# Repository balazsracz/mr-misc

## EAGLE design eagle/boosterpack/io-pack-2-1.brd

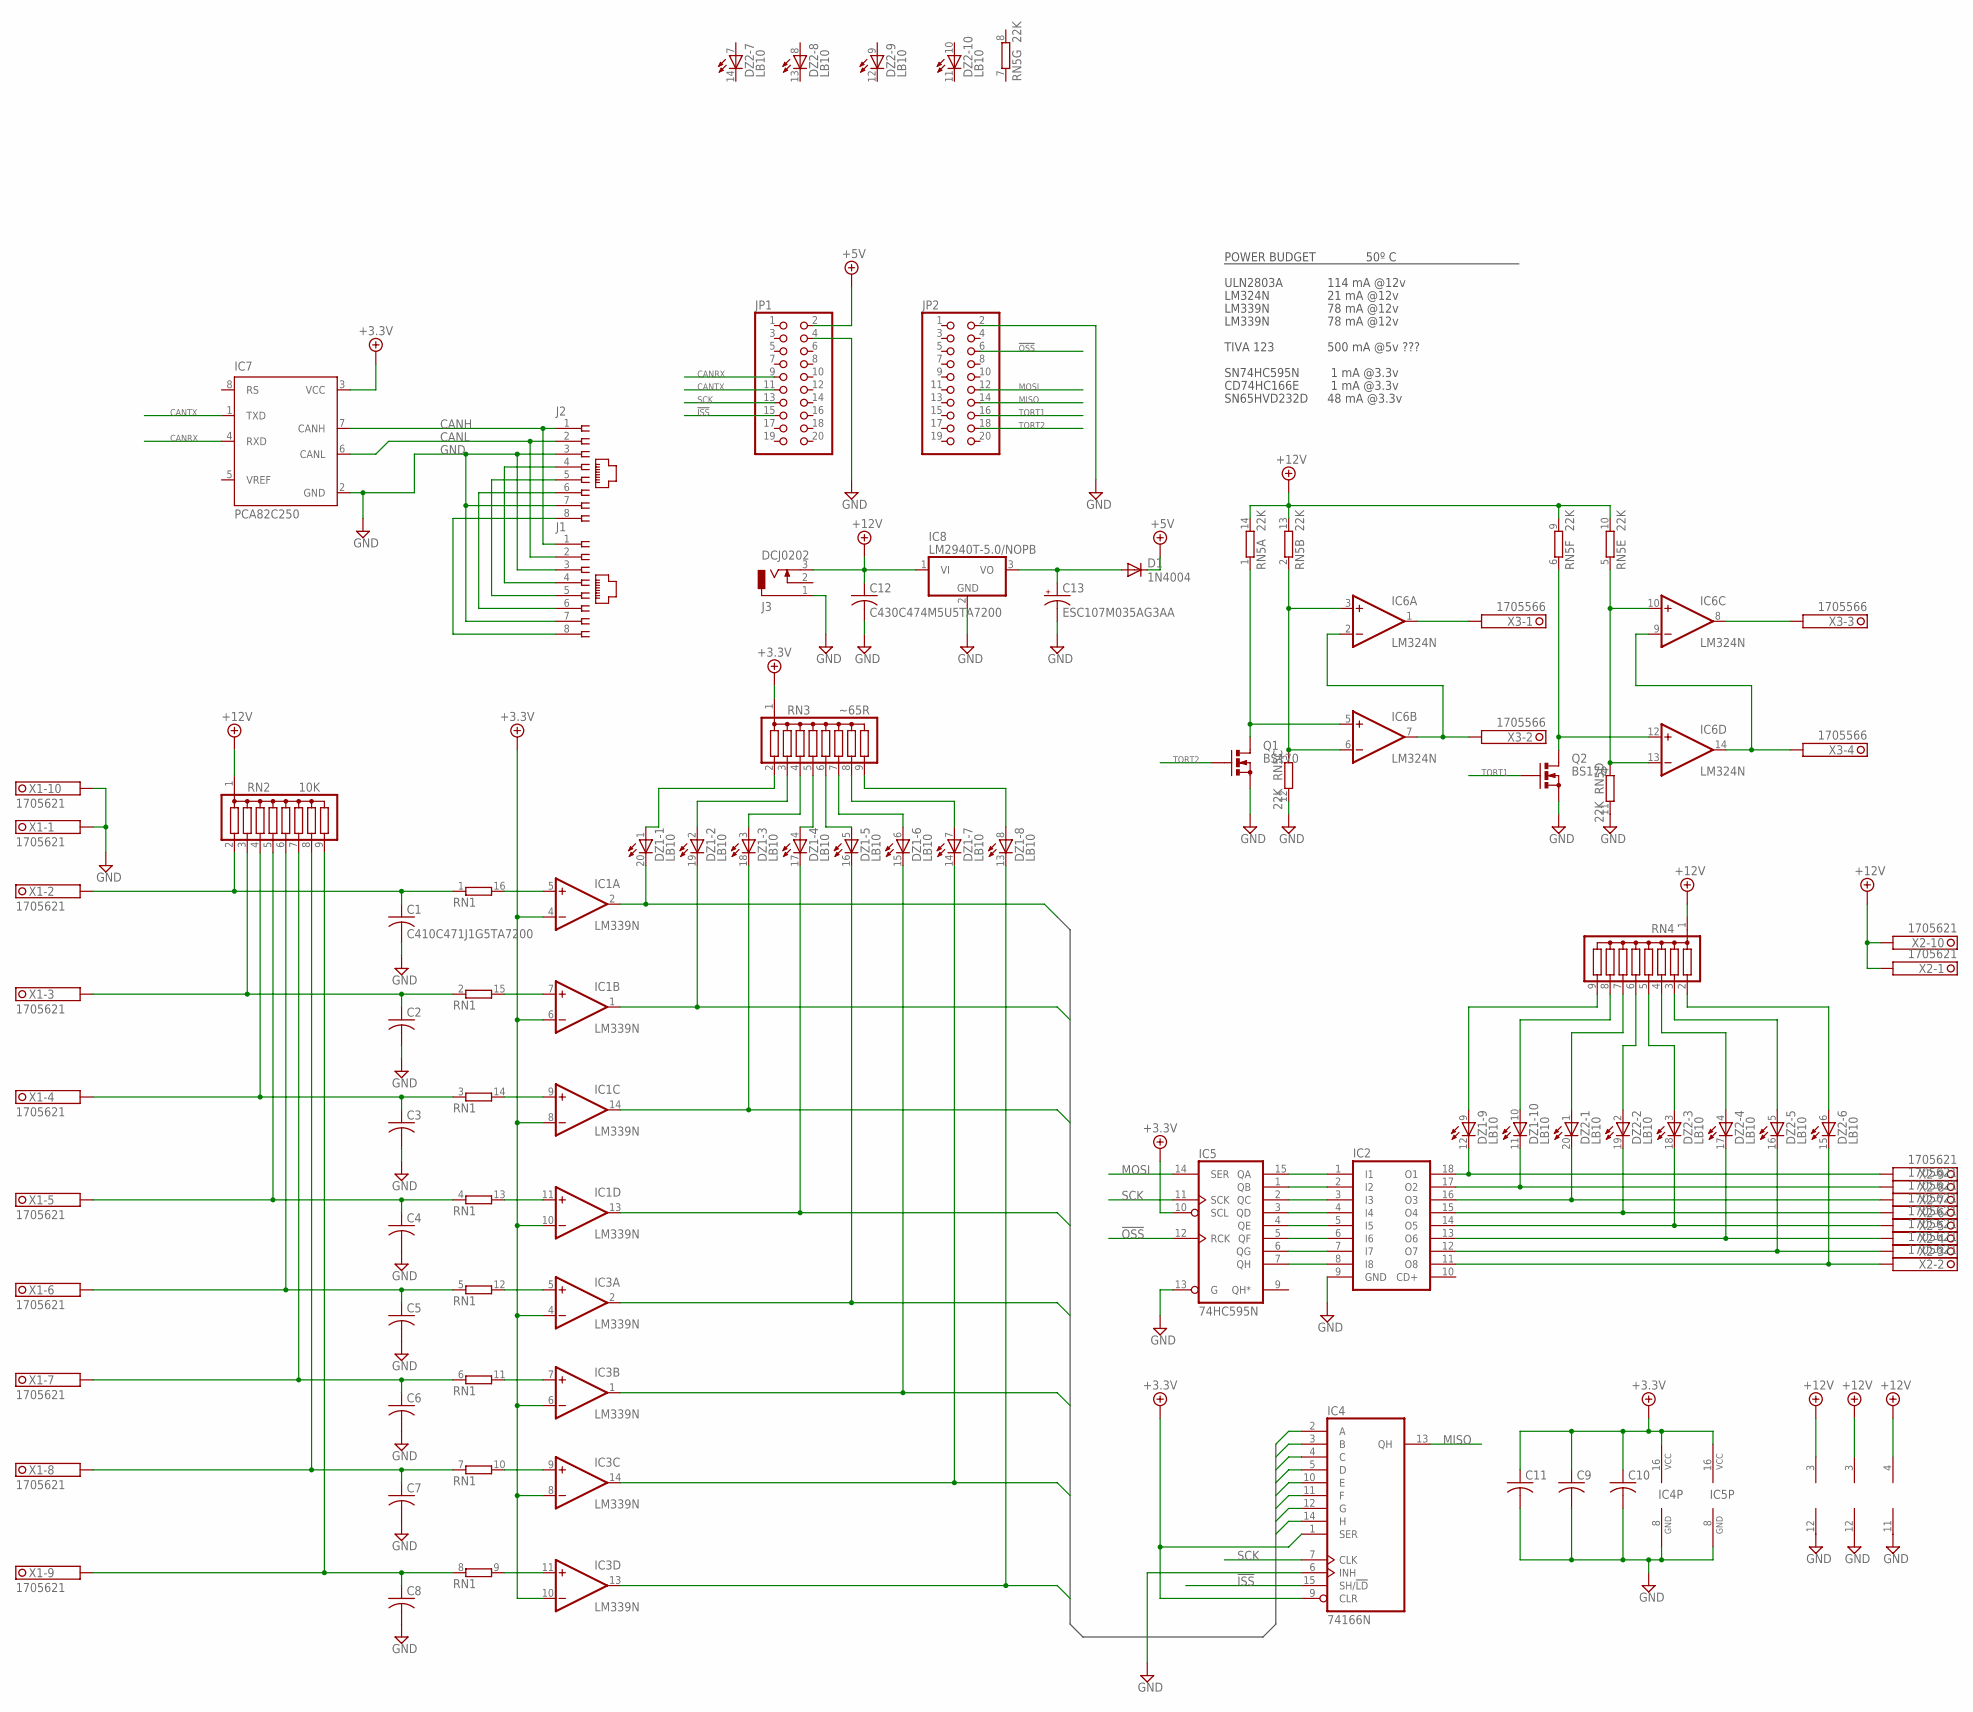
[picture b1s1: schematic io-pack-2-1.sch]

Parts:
C1: C410C471J1G5TA7200; C050-025X075
C2, C3, C4, C5, C6, C7, C8, C9, C10, C11: C-US050-025X075; C050-025X075
C12: C430C474M5U5TA7200; C075-032X103
C13: ESC107M035AG3AA; E3,5-8
D1: 1N4004; DO41-10
DZ1, DZ2: LB10
IC1, IC3: LM339N; DIL14
IC2: ULN2803A; DIL18
IC4: 74166N; DIL16
IC5: 74HC595N; DIL16
IC6: LM324N; DIL14
IC7: PCA82C250; DIL08
IC8: LM2940T-5.0/NOPB; TO220V
J1, J2: 555164-1
J3: DCJ0202
JP1, JP2: PINHD-2X10; 2X10
Q1, Q2: BS170; SOT54E
RN1: 8R-P; DIL16
RN2: 10K; SIL9
RN3: ~65R; SIL9
RN4: G08R; SIL9
RN5: 22K; DIL14
X1, X2: 1705621
X3: 1705566

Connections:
!ISS: IC4.15 (SH/!LD), JP1.15
!OSS: IC5.12 (RCK), JP2.6
+3.3V: C9.1, C10.1, C11.1, IC1.4 (-IN), IC1.6 (-IN), IC1.8 (-IN), IC1.10 (-IN), IC3.4 (-IN), IC3.6 (-IN), IC3.8 (-IN), IC3.10 (-IN), IC4.1 (SER), IC4.9 (CLR), IC4.16 (VCC), IC5.10 (SCL), IC5.16 (VCC), IC7.3 (VCC), RN3.1
+5V: D1.C, JP1.2
+12V: C12.1, IC1.3 (V+), IC3.3 (V+), IC6.4 (V+), IC8.1 (VI), J3.3, RN2.1, RN4.1, RN5.9 (2), RN5.10 (2), RN5.13 (2), RN5.14 (2), X2.1.1, X2.1.2, X2.10.1, X2.10.2
CANH: IC7.7 (CANH), J1.1, J2.1
CANL: IC7.6 (CANL), J1.2, J2.2
CANRX: IC7.4 (RXD), JP1.9
CANTX: IC7.1 (TXD), JP1.11
GND: C1.2, C2.2, C3.2, C4.2, C5.2, C6.2, C7.2, C8.2, C9.2, C10.2, C11.2, C12.2, C13.-, IC1.12 (GND), IC2.9 (GND), IC3.12 (GND), IC4.6 (INH), IC4.8 (GND), IC5.8 (GND), IC5.13 (G), IC6.11 (V-), IC7.2 (GND), IC8.2 (GND), J1.3, J1.7, J2.3, J2.7, J3.1, JP1.4, JP2.2, Q1.S, Q2.S, RN5.11 (2), RN5.12 (2), X1.1.1, X1.1.2, X1.10.1, X1.10.2
IN0: DZ1.20 (C), IC1.2 (OUT), IC4.2 (A)
IN1: DZ1.19 (C), IC1.1 (OUT), IC4.3 (B)
IN2: DZ1.18 (C), IC1.14 (OUT), IC4.4 (C)
IN3: DZ1.17 (C), IC1.13 (OUT), IC4.5 (D)
IN4: DZ1.16 (C), IC3.2 (OUT), IC4.10 (E)
IN5: DZ1.15 (C), IC3.1 (OUT), IC4.11 (F)
IN6: DZ1.14 (C), IC3.14 (OUT), IC4.12 (G)
IN7: DZ1.13 (C), IC3.13 (OUT), IC4.14 (H)
MISO: IC4.13 (QH), JP2.14
MOSI: IC5.14 (SER), JP2.12
unnamed: C13.+, D1.A, IC8.3 (VO)
unnamed: J1.4, J2.4
unnamed: J1.5, J2.5
unnamed: J1.6, J2.6
unnamed: IC1.5 (+IN), RN1.16 (2)
unnamed: IC1.7 (+IN), RN1.15 (2)
unnamed: IC1.9 (+IN), RN1.14 (2)
unnamed: IC1.11 (+IN), RN1.13 (2)
unnamed: DZ1.1 (A), RN3.2
unnamed: DZ1.2 (A), RN3.3
unnamed: DZ1.3 (A), RN3.4
unnamed: DZ1.4 (A), RN3.5
unnamed: DZ1.5 (A), RN3.6
unnamed: DZ1.6 (A), RN3.7
unnamed: DZ1.7 (A), RN3.8
unnamed: DZ1.8 (A), RN3.9
unnamed: IC2.1 (I1), IC5.15 (QA)
unnamed: IC2.2 (I2), IC5.1 (QB)
unnamed: IC2.3 (I3), IC5.2 (QC)
unnamed: IC2.4 (I4), IC5.3 (QD)
unnamed: C1.1, RN1.1, RN2.2, X1.2.1, X1.2.2
unnamed: C2.1, RN1.2 (1), RN2.3, X1.3.1, X1.3.2
unnamed: C3.1, RN1.3 (1), RN2.4, X1.4.1, X1.4.2
unnamed: C4.1, RN1.4 (1), RN2.5, X1.5.1, X1.5.2
unnamed: IC3.5 (+IN), RN1.12 (2)
unnamed: IC3.7 (+IN), RN1.11 (2)
unnamed: IC3.9 (+IN), RN1.10 (2)
unnamed: IC3.11 (+IN), RN1.9 (2)
unnamed: C5.1, RN1.5 (1), RN2.6, X1.6.1, X1.6.2
unnamed: C6.1, RN1.6 (1), RN2.7, X1.7.1, X1.7.2
unnamed: C7.1, RN1.7 (1), RN2.8, X1.8.1, X1.8.2
unnamed: C8.1, RN1.8 (1), RN2.9, X1.9.1, X1.9.2
unnamed: IC2.5 (I5), IC5.4 (QE)
unnamed: IC2.6 (I6), IC5.5 (QF)
unnamed: IC2.7 (I7), IC5.6 (QG)
unnamed: IC2.8 (I8), IC5.7 (QH)
unnamed: IC6.3 (+IN), IC6.6 (-IN), RN5.2 (1), RN5.3 (1)
unnamed: DZ1.12 (C), IC2.18 (O1), X2.9.1, X2.9.2
unnamed: DZ1.9 (A), RN4.9
unnamed: DZ1.10 (A), RN4.8
unnamed: DZ2.1 (A), RN4.7
unnamed: DZ2.2 (A), RN4.6
unnamed: DZ2.3 (A), RN4.5
unnamed: DZ2.4 (A), RN4.4
unnamed: DZ2.5 (A), RN4.3
unnamed: DZ2.6 (A), RN4.2
unnamed: DZ1.11 (C), IC2.17 (O2), X2.8.1, X2.8.2
unnamed: DZ2.20 (C), IC2.16 (O3), X2.7.1, X2.7.2
unnamed: DZ2.19 (C), IC2.15 (O4), X2.6.1, X2.6.2
unnamed: DZ2.18 (C), IC2.14 (O5), X2.5.1, X2.5.2
unnamed: DZ2.17 (C), IC2.13 (O6), X2.4.1, X2.4.2
unnamed: DZ2.16 (C), IC2.12 (O7), X2.3.1, X2.3.2
unnamed: DZ2.15 (C), IC2.11 (O8), X2.2.1, X2.2.2
unnamed: IC6.5 (+IN), Q1.D, RN5.1
unnamed: IC6.2 (-IN), IC6.7 (OUT), X3.2.1, X3.2.2
unnamed: IC6.12 (+IN), Q2.D, RN5.6 (1)
unnamed: IC6.10 (+IN), IC6.13 (-IN), RN5.4 (1), RN5.5 (1)
unnamed: IC6.9 (-IN), IC6.14 (OUT), X3.4.1, X3.4.2
unnamed: IC6.1 (OUT), X3.1.1, X3.1.2
unnamed: IC6.8 (OUT), X3.3.1, X3.3.2
PWR_POS: J1.8, J2.8
SCK: IC4.7 (CLK), IC5.11 (SCK), JP1.13
TORT1: JP2.16, Q2.G
TORT2: JP2.18, Q1.G

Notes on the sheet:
POWER BUDGET
ULN2803A
114 mA @12v
50º C
LM324N
21 mA @12v
LM339N
78 mA @12v
SN74HC595N
CD74HC166E
SN65HVD232D
TIVA 123
1 mA @3.3v
48 mA @3.3v
500 mA @5v ???

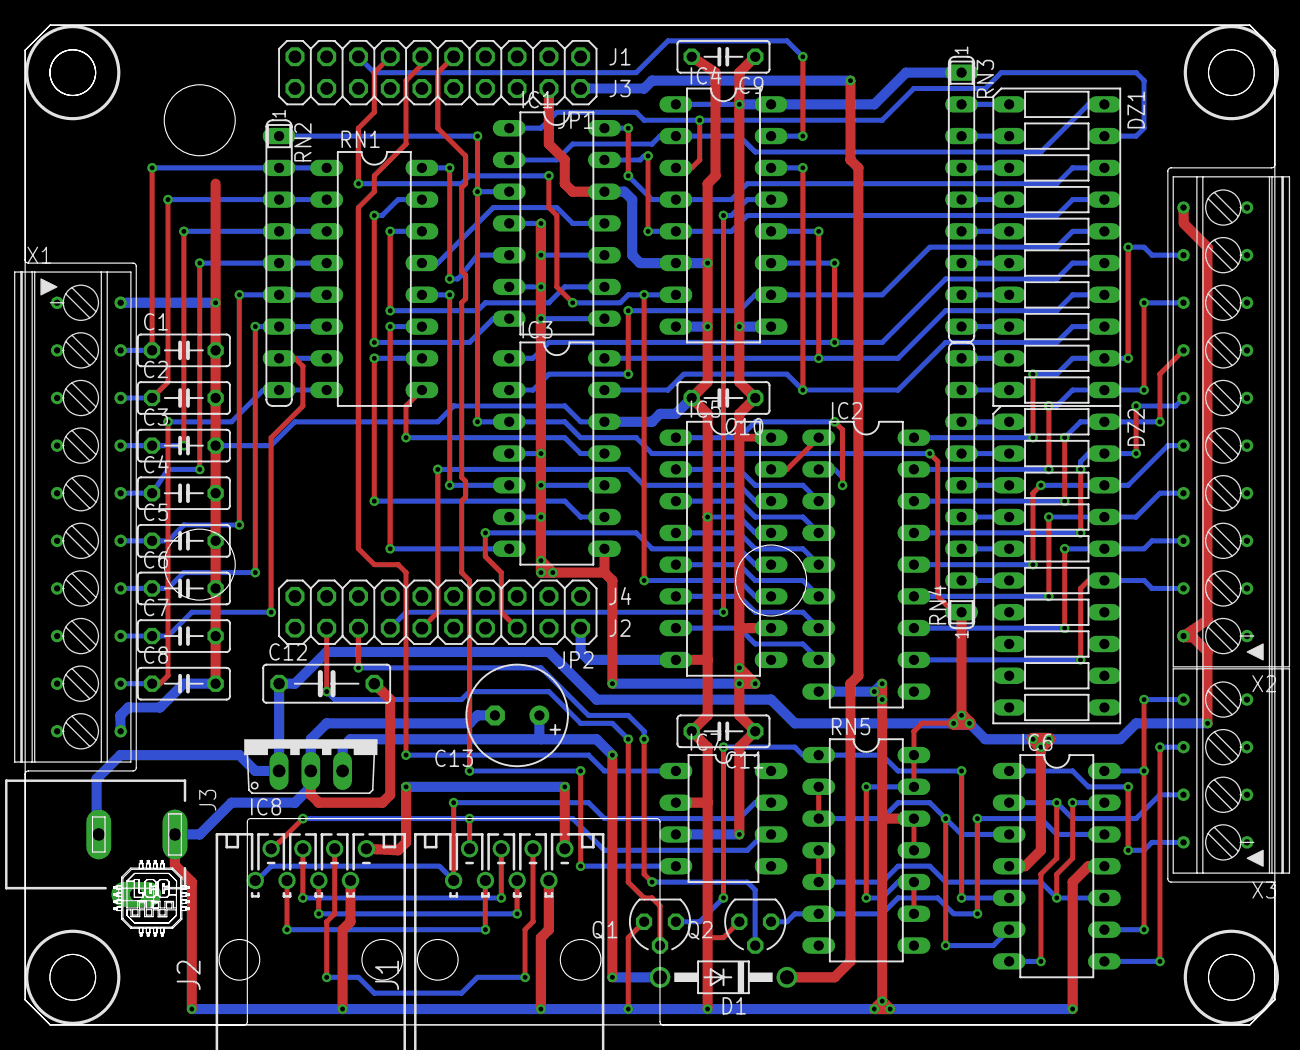
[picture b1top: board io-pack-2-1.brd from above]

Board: 2 copper layers, 100.0 x 80.0 mm, 39 parts (0 on the bottom side), 84 nets.

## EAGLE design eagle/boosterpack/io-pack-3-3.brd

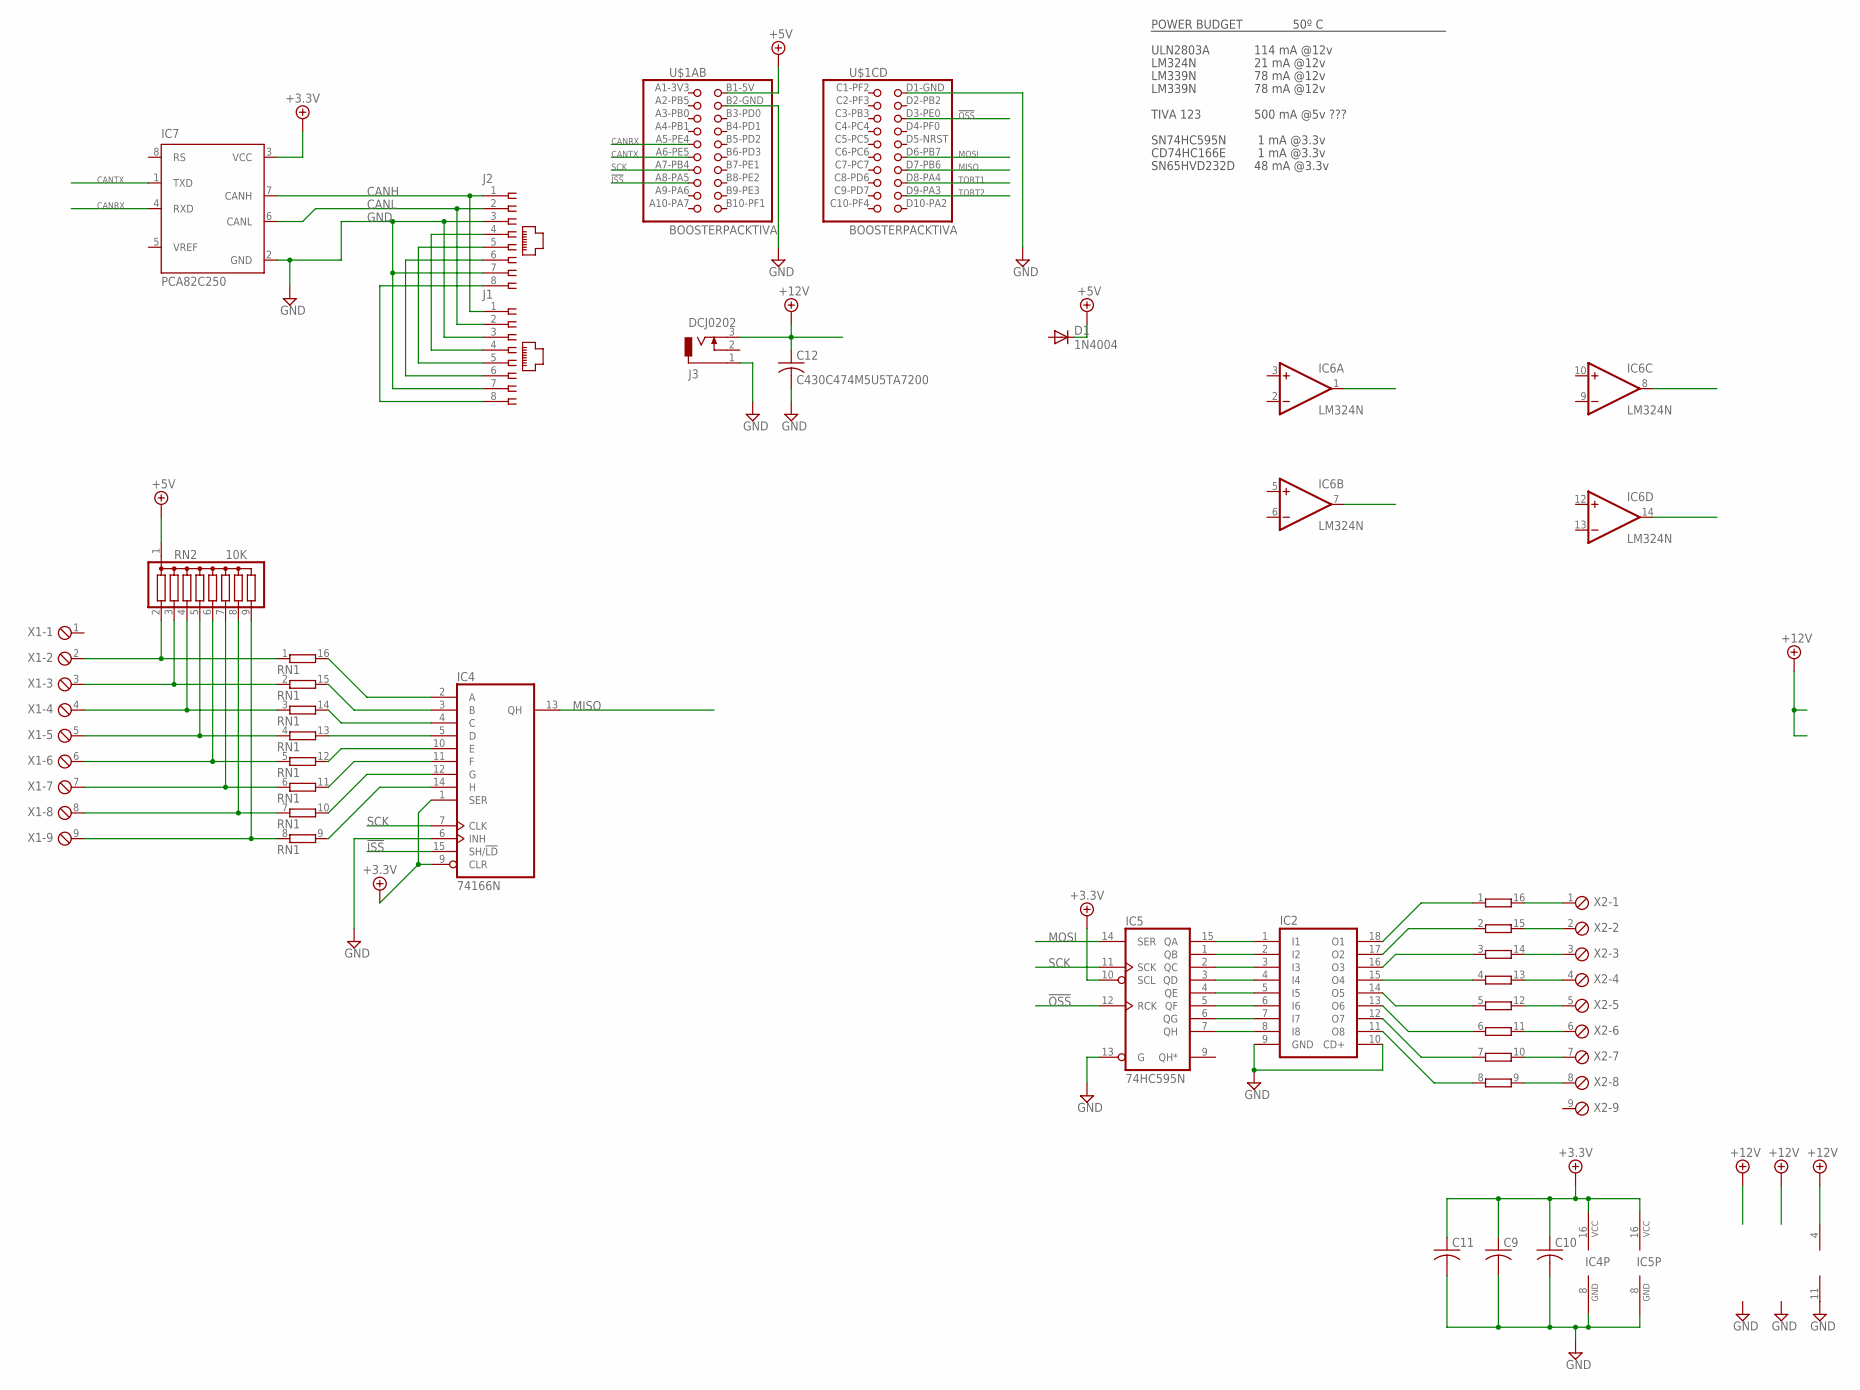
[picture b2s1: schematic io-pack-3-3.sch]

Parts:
C9, C10, C11: C-US050-025X075; C050-025X075
C12: C430C474M5U5TA7200; C075-032X103
D1: 1N4004; DO41-10
IC2: ULN2803A; DIL18
IC4: 74166N; DIL16
IC5: 74HC595N; DIL16
IC6: LM324N; DIL14
IC7: PCA82C250; DIL08
J1, J2: 555164-1
J3: DCJ0202
RN1, RN3: 8R-P; DIL16
RN2: 10K; SIL9
U$1: BOOSTERPACKTIVA; BOOSTERPACK-TIVA
X1, X2: MPT9; 9POL254

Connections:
!ISS: IC4.15 (SH/!LD), U$1.A8-PA5 (15)
!OSS: IC5.12 (RCK), U$1.D3-PE0 (6)
+3.3V: C9.1, C10.1, C11.1, IC4.1 (SER), IC4.9 (CLR), IC4.16 (VCC), IC5.10 (SCL), IC5.16 (VCC), IC7.3 (VCC)
+5V: D1.C, RN2.1, U$1.B1-5V (2)
+12V: C12.1, IC6.4 (V+), J3.3
CANH: IC7.7 (CANH), J1.1, J2.1
CANL: IC7.6 (CANL), J1.2, J2.2
CANRX: IC7.4 (RXD), U$1.A5-PE4 (9)
CANTX: IC7.1 (TXD), U$1.A6-PE5 (11)
GND: C9.2, C10.2, C11.2, C12.2, IC2.9 (GND), IC2.10 (CD+), IC4.6 (INH), IC4.8 (GND), IC5.8 (GND), IC5.13 (G), IC6.11 (V-), IC7.2 (GND), J1.3, J1.7, J2.3, J2.7, J3.1, U$1.B2-GND (4), U$1.D1-GND (2)
MISO: IC4.13 (QH), U$1.D7-PB6 (14)
MOSI: IC5.14 (SER), U$1.D6-PB7 (12)
unnamed: IC2.18 (O1), RN3.1
unnamed: IC2.17 (O2), RN3.2 (1)
unnamed: IC2.16 (O3), RN3.3 (1)
unnamed: J1.4, J2.4
unnamed: J1.5, J2.5
unnamed: J1.6, J2.6
unnamed: IC2.15 (O4), RN3.4 (1)
unnamed: IC2.14 (O5), RN3.5 (1)
unnamed: IC2.13 (O6), RN3.6 (1)
unnamed: IC2.12 (O7), RN3.7 (1)
unnamed: IC2.11 (O8), RN3.8 (1)
unnamed: RN3.16 (2), X2.1
unnamed: RN3.15 (2), X2.2
unnamed: RN3.14 (2), X2.3
unnamed: RN3.13 (2), X2.4
unnamed: RN3.12 (2), X2.5
unnamed: RN3.11 (2), X2.6
unnamed: RN3.10 (2), X2.7
unnamed: RN3.9 (2), X2.8
unnamed: IC2.1 (I1), IC5.15 (QA)
unnamed: IC2.2 (I2), IC5.1 (QB)
unnamed: IC2.3 (I3), IC5.2 (QC)
unnamed: IC2.4 (I4), IC5.3 (QD)
unnamed: RN1.1, RN2.2, X1.2
unnamed: RN1.2 (1), RN2.3, X1.3
unnamed: RN1.3 (1), RN2.4, X1.4
unnamed: RN1.4 (1), RN2.5, X1.5
unnamed: RN1.5 (1), RN2.6, X1.6
unnamed: RN1.6 (1), RN2.7, X1.7
unnamed: RN1.7 (1), RN2.8, X1.8
unnamed: RN1.8 (1), RN2.9, X1.9
unnamed: IC2.5 (I5), IC5.4 (QE)
unnamed: IC2.6 (I6), IC5.5 (QF)
unnamed: IC2.7 (I7), IC5.6 (QG)
unnamed: IC2.8 (I8), IC5.7 (QH)
unnamed: IC4.2 (A), RN1.16 (2)
unnamed: IC4.3 (B), RN1.15 (2)
unnamed: IC4.4 (C), RN1.14 (2)
unnamed: IC4.5 (D), RN1.13 (2)
unnamed: IC4.10 (E), RN1.12 (2)
unnamed: IC4.11 (F), RN1.11 (2)
unnamed: IC4.12 (G), RN1.10 (2)
unnamed: IC4.14 (H), RN1.9 (2)
PWR_POS: J1.8, J2.8
SCK: IC4.7 (CLK), IC5.11 (SCK), U$1.A7-PB4 (13)
TORT1: U$1.D8-PA4 (16)
TORT2: U$1.D9-PA3 (18)

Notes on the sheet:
POWER BUDGET
ULN2803A
114 mA @12v
50º C
LM324N
21 mA @12v
LM339N
78 mA @12v
SN74HC595N
CD74HC166E
SN65HVD232D
TIVA 123
1 mA @3.3v
48 mA @3.3v
500 mA @5v ???

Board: 2 copper layers, 19 parts (0 on the bottom side), 57 nets, no tracks yet.
